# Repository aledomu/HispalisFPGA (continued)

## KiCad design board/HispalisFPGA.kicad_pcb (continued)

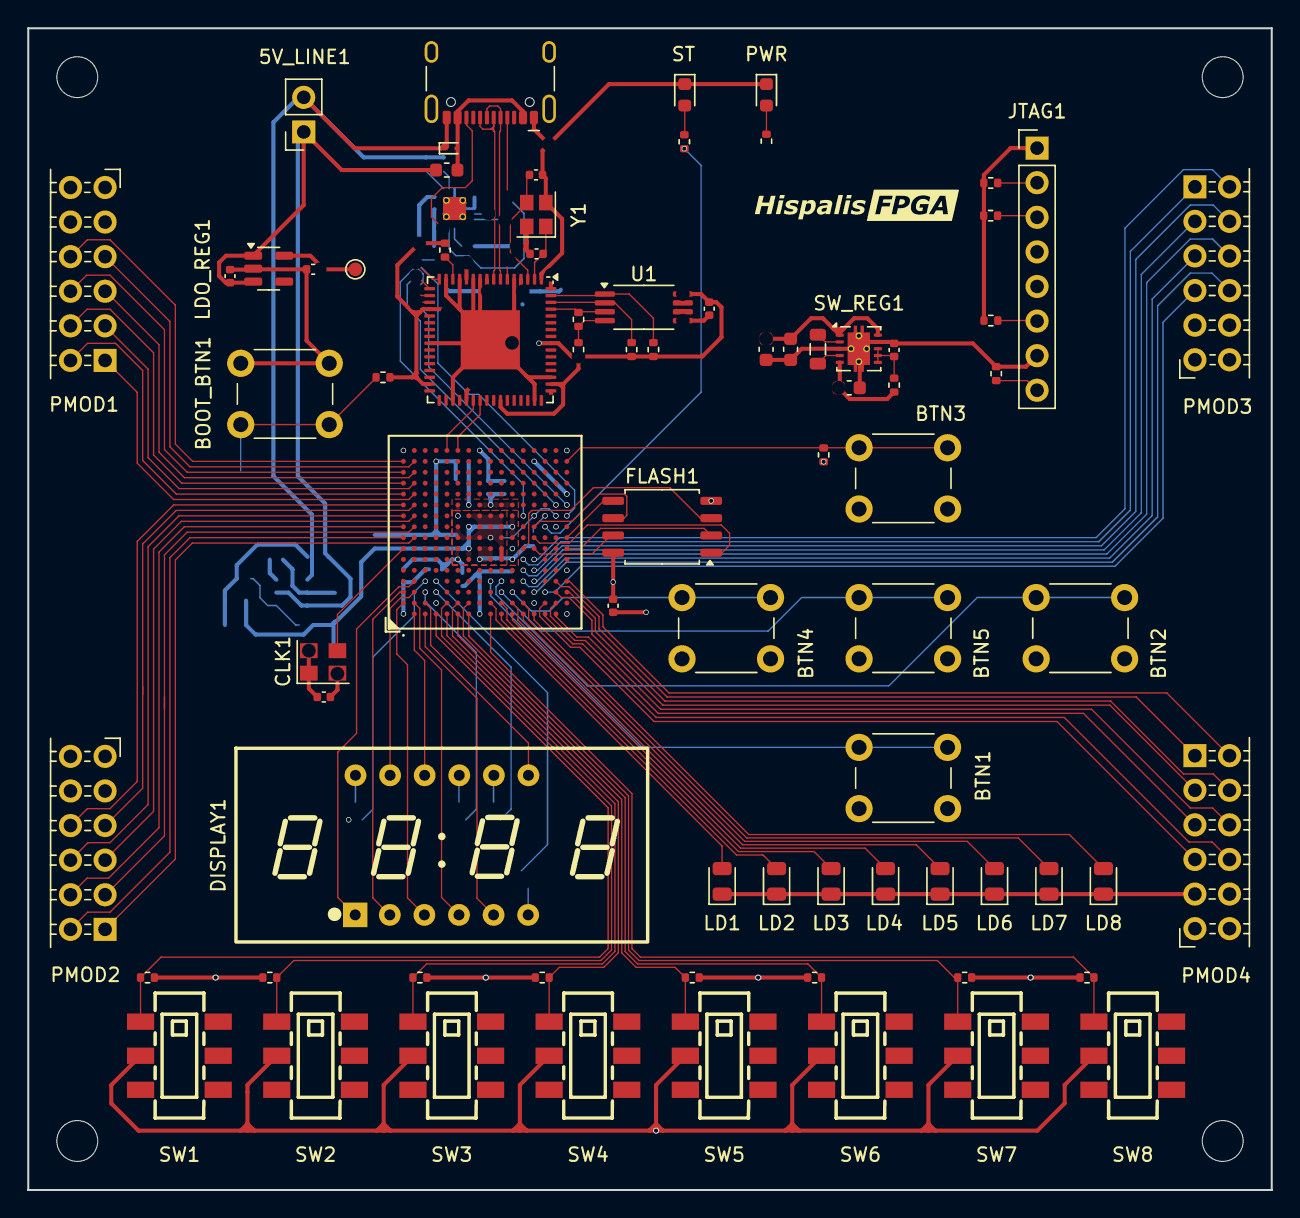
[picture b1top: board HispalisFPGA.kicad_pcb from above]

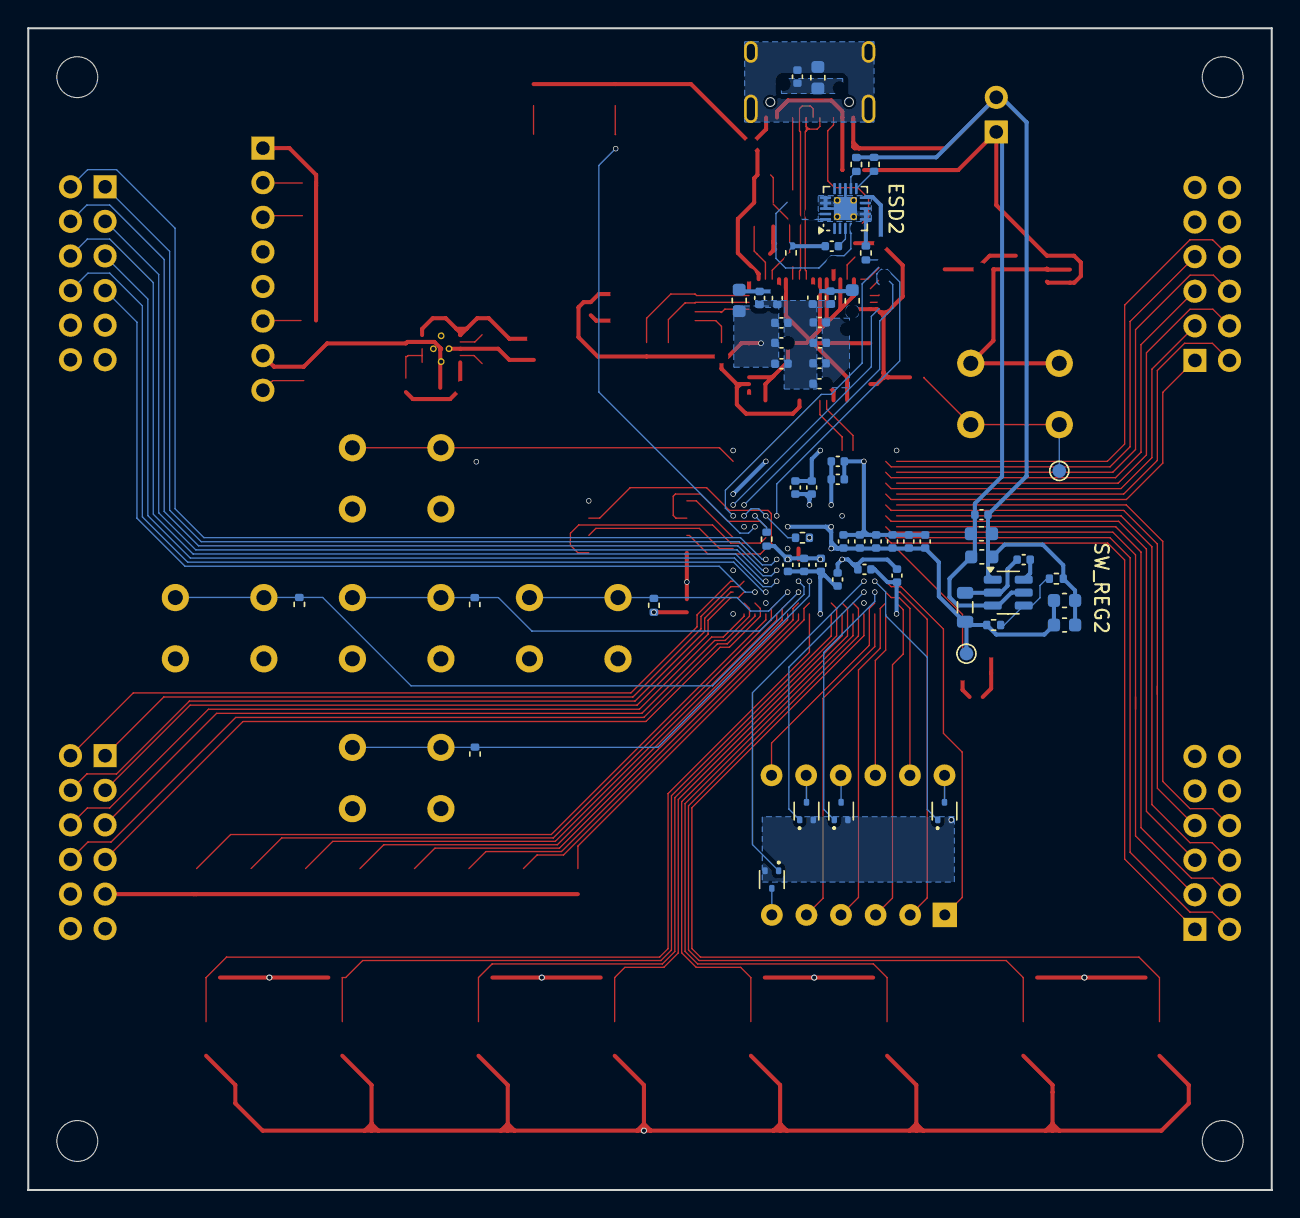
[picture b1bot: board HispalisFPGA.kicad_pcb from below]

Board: 4 copper layers, 91.3 x 85.3 mm, 141 parts (59 on the bottom side), 119 nets.

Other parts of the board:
HISPALISFPGA-LOGO1: HISPALISFPGA-LOGO; HispalisFPGA-Logo
MH01, MH02, MH03, MH04: MountingHole_3mm

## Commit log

2024-04-03 Rename and update project
2024-04-08 Add PMODs, LEDs, switches and buttons
2024-04-11 Add 7-segment 4-digit display and annotate components
2024-04-24 Fix and adjust power connections
2024-04-25 Fix LEDs polarity
2024-04-26 Add socket wire for 5V power input-output
2024-04-30 Simplify USB connections
2024-05-02 Assign generic footprints
2024-05-03 Cleanup unused symbols
2024-05-03 Re-annotate schematic and fix broken wires
2024-05-03 Rearrange USB connections
2024-05-06 Fix power connections
2024-05-06 Check clocks
2024-05-31 Component selection for assembly
2024-05-31 Remove unnecessary resistors for LEDs
2024-06-03 Power and status LED correction
2024-06-06 Improve USB port protections
2024-06-07 Make all display pins activate on high signal from FPGA pins
2024-06-10 Fix resistor value
2024-06-11 Replace SPI flash device for a cheaper one
2024-06-14 Remove SDRAM block
2024-06-14 Rearrange, cleanup and reannotate schematic
2024-06-17 Replace 1.1V regulator
2024-06-18 Add missing ESD on 5V power line
2024-06-18 Cleanup repository
2024-06-18 Regenerate PCB layout file
2024-06-19 Set manufacturer constraints and track widths
2024-06-24 Final connection of ECP5 chip
2024-10-02 Change USB 3.1 for USB 2.0 Type-C and use JTAG and serial USB controller
2024-10-02 Subdivide schematic
2024-10-04 Complete schematic
2024-10-10 Finish routing and remove unneeded silkscreen
2024-10-17 No errors
2024-10-21 No warnings
2024-10-21 Add metadata
2024-10-30 Add logo
2025-01-14 Further adaptations for JLCPCB order
2025-01-14 Move logo footprint to the right directory
2025-01-14 Fix USB connector margin between pads and holes
2025-01-14 Fix 1.1V regulator reference
2025-01-14 Remove empty project symbol library
2025-01-14 Change switches
2025-02-10 Set display symbol and footprint from EasyEDA
2025-02-10 Change LFE5U chip from BGA381 to BGA256 package
2025-04-14 Change JTAG pin header parts reference
